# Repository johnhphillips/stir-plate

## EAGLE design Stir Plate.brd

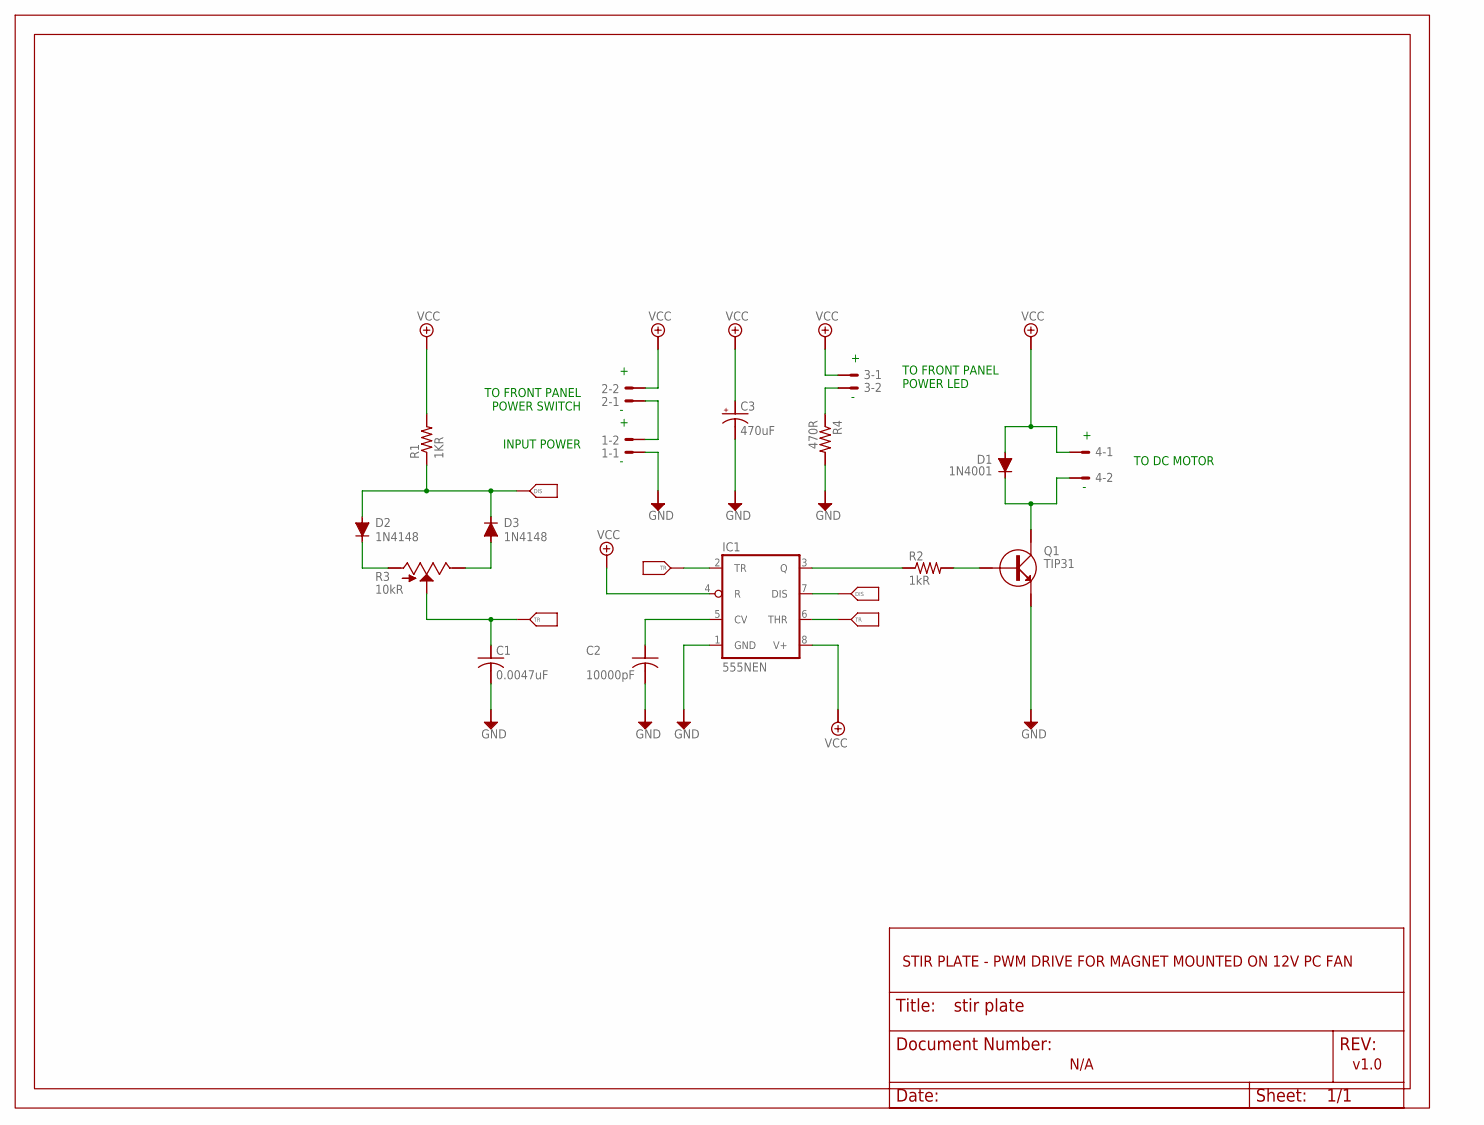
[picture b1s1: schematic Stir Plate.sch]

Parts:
1, 2, 3, 4: 22-23-2021
C1: 0.0047uF; C025-030X050
C2: 10000pF; C025-030X050
C3: 470uF; E2-5
D1: 1N4001; DO41-10
D2, D3: 1N4148; DO35-7
FRAME1: FRAME_A_L
IC1: 555NEN; DIL08
Q1: TIP31; TO220AV
R1: 1KR; 0207/10
R2: 1kR; 0207/10
R3: 10kR; 3RP/1610N
R4: 470R; 0207/10
U$1: DOCFIELD

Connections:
+12V: 2.2, 3.1, 4.1, C3.+, D1.A, IC1.4 (R), IC1.8 (V+), R1.2
GND: 1.1, C1.2, C2.2, C3.-, IC1.1 (GND), Q1.E, R4.2
unnamed: 1.2, 2.1
unnamed: 4.2, D1.C, Q1.C
unnamed: D2.A, D3.C, IC1.7 (DIS), R1.1
unnamed: D3.A, R3.2 (E)
unnamed: D2.C, R3.1 (A)
unnamed: IC1.2 (TR), IC1.6 (THR)
unnamed: C2.1, IC1.5 (CV)
unnamed: IC1.3 (Q), R2.1
unnamed: Q1.B, R2.2
unnamed: C1.1, R3.3 (S)
unnamed: 3.2, R4.1

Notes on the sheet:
INPUT POWER
TO FRONT PANEL POWER SWITCH
TO FRONT PANEL POWER LED
TO DC MOTOR
STIR PLATE - PWM DRIVE FOR MAGNET MOUNTED ON 12V PC FAN
N/A
v1.0

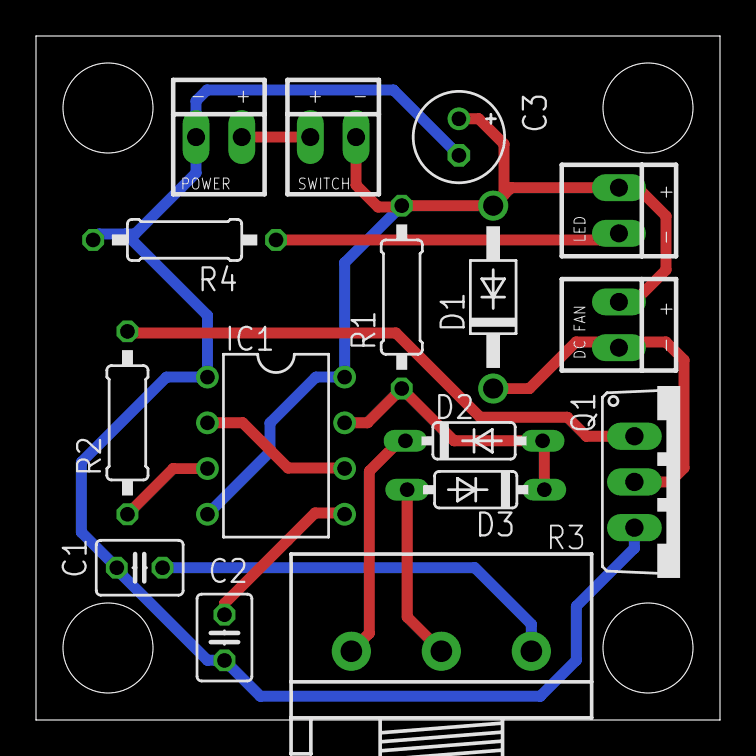
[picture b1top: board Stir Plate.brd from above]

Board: 2 copper layers, 38.0 x 38.0 mm, 18 parts (0 on the bottom side), 13 nets.

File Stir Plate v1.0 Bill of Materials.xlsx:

Name | Notes | Part Number | Source | Amount | Unit Cost | Line Cost
1L Erlenmeyer Flask |  |  | Amazon | 1 | 14 | 14
1 x 3/8" Spinbar |  |  | Amazon | 1 | 6.5 | 6.5
12VDC 1A Wall Adapter |  |  | Amazon | 1 | 5.09 | 5.09
Neodymium Magnet (1" x 1/4" x 1/4") | Sold in pack of 6 |  | Amazon | 1 | 1.63 | 1.63
Printed Circuit Board | Sold in pack of 3 |  | OSH Park | 1 | 3.73 | 3.73
Project Enclosure (6" x 4" x 2") |  |  | Radio Shack | 1 | 6.49 | 6.49
Hexagonal Control Knob |  | 45KN013-GRX | Mouser | 1 | 0.84 | 0.84
Toggle Switch w/ Label Plate |  | 103-0132-EVX | Mouser | 1 | 2.6 | 2.6
LED Panel Mount Indicators 5mm HE Red |  | 749-MPR5HD | Mouser | 1 | 1.96 | 1.96
DC Power Connectors Panel Mount 2.1mm |  | 163-R123B-E | Mouser | 1 | 1.9 | 1.9
Ceramic Disk Capacitor (0.0047uF) |  | K473K15X7RF5TL2 | Digikey | 1 | 0.37 | 0.37
Electrolytic Capacitor (470uF) |  | 493-1269-ND | Digikey | 1 | 0.2 | 0.2
12VDC Brushless Fan (80mm) |  | 259-1462-ND | Digikey | 1 | 2.52 | 2.52
Rotary Poteniometer (10kR) |  | 987-1301-ND | Digikey | 1 | 0.72 | 0.72
Small Signal Diode |  | 1N4148TACT-ND | Digikey | 2 | 5.28E-2 | 0.1056
Ceramic Disk Capacitor (10000pF) |  | 1103PHCT-ND | Digikey | 1 | 0.23899999999999999 | 0.23899999999999999
555 Timer IC |  | IRF520PBF-ND | Digikey | 1 | 0.3 | 0.3
Flyback Diode (General Purpose) |  | 1N4001FSCT-ND | Digikey | 1 | 0.152 | 0.152
NPN Transistor |  | TIP31CFS-ND | Digikey | 1 | 0.54 | 0.54
Resistor (1kR / 0.25W) |  | CF14JT1K00 | Digikey | 2 | 0.08 | 0.16
Resistor (470R / 1W) |  | FMP100JR-52-470R | Digikey | 1 | 0.14000000000000001 | 0.14000000000000001
 |  |  |  |  | Subtotal | 50.186599999999999
 |  |  |  |  | CA 7.5% Sales Tax | 3.7639949999999995
 |  |  |  |  | Total | 53.950595
Note: Will end up with 6 magnets and 3 PCBs excess assuming only one of each ot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

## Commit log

2014-03-27 Added Bill of Materials
2014-04-04 Ground Plane corrected
2014-05-12 BOM Formatting
2014-05-13 Correct Pot footprint / library entry
    TODO: Fix board
2014-05-14 Fixed board layout
